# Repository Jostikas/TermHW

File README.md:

Oven thermometer from an ESP8266. HW only for now.

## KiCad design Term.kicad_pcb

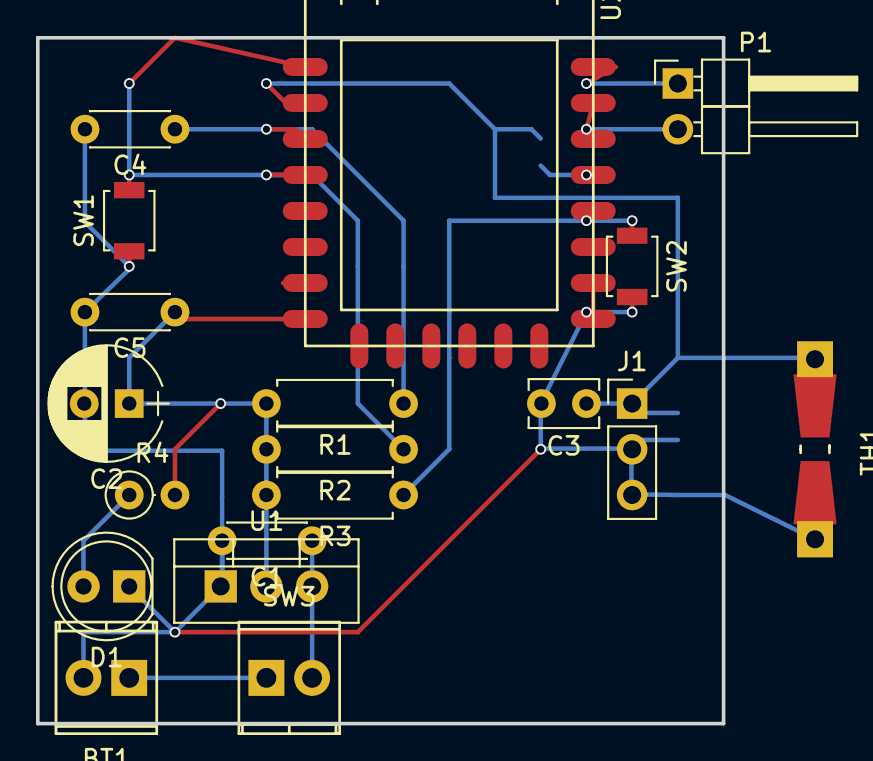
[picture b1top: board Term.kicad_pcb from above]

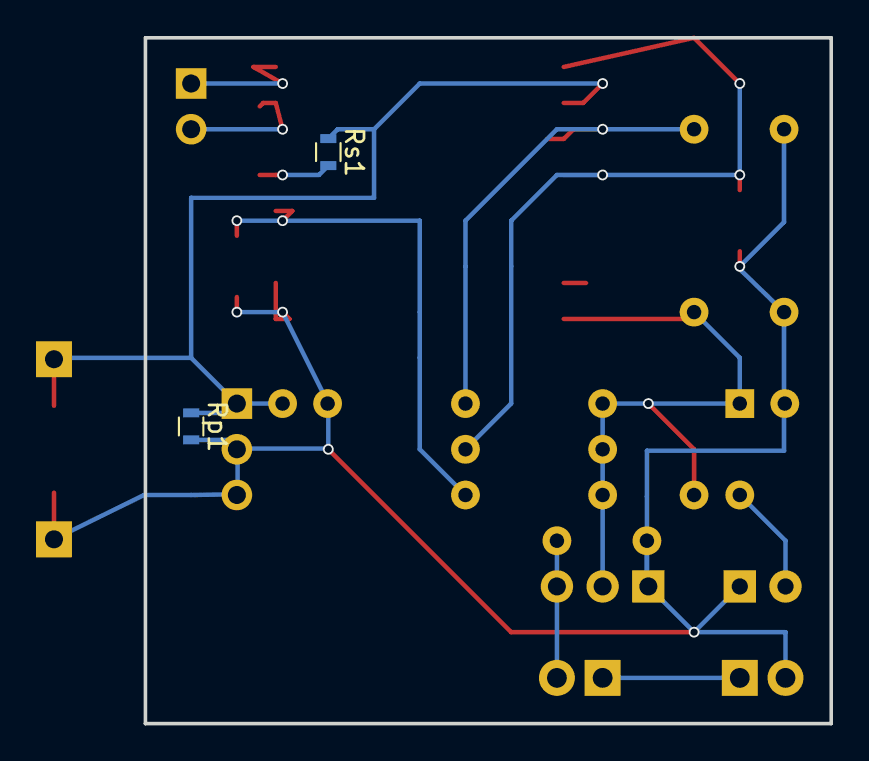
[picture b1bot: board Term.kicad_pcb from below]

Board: 2 copper layers, 38.1 x 38.1 mm, 21 parts (2 on the bottom side), 12 nets.

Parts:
BT1: 4x1.5V; TerminalBlock_Pheonix_MPT-2.54mm_2pol
C1: 100n; C_Disc_D4.3mm_W1.9mm_P5.00mm
C2: 10u; CP_Radial_D6.3mm_P2.50mm
C3: 33n; C_Disc_D3.8mm_W2.6mm_P2.50mm
C4: 10n; C_Disc_D4.3mm_W1.9mm_P5.00mm
C5: 47n; C_Disc_D4.3mm_W1.9mm_P5.00mm
D1: LED_ALT; LED_D5.0mm
J1: JACK_TRS; Pin_Header_Straight_1x03_Pitch2.54mm
P1: UART0; Pin_Header_Angled_1x02_Pitch2.54mm
R1: 100k; R_Axial_DIN0207_L6.3mm_D2.5mm_P7.62mm_Horizontal
R2, R3: 22k; R_Axial_DIN0207_L6.3mm_D2.5mm_P7.62mm_Horizontal
R4: 2k2; R_Axial_DIN0207_L6.3mm_D2.5mm_P2.54mm_Vertical
Rp1: 15k; R_0603
Rs1: 33k; R_0603
SW1: RESET; SW_SPST_B3U-1000P
SW2: FLASH; SW_SPST_B3U-1000P
SW3: SW_SPST; TerminalBlock_Pheonix_MPT-2.54mm_2pol
TH1: Thermistor_NTC; Resistor_SMD+THTuniversal_0805to1206_RM10_HandSoldering
U1: LM1117-3.3; TO-220_Vertical
U2: ESP-12F

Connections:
+3V3: C2.1, C5.1, R1.2, R2.2, R3.2, R4.2, U1.2, U2.8
/ADC: C3.1, J1.1, Rp1.1, Rs1.1, TH1.1, U2.2
/SENSE_PWR: Rs1.2, U2.19
/~RST: R2.1, SW1.2, U2.1, U2.4
GND: BT1.2, C1.2, C2.2, C3.2, C4.2, C5.2, D1.1, J1.2, J1.3, Rp1.2, SW1.1, SW2.2, TH1.2, U1.1, U2.15, U2.16
unnamed: BT1.1, SW3.1
unnamed: C1.1, SW3.2, U1.3
unnamed: C4.1, R1.1, U2.3
unnamed: D1.2, R4.1
unnamed: P1.1, U2.22
unnamed: P1.2, U2.21
unnamed: R3.1, SW2.1, U2.18

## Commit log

2017-05-12 v0.1 - Connection and deep sleep work.
